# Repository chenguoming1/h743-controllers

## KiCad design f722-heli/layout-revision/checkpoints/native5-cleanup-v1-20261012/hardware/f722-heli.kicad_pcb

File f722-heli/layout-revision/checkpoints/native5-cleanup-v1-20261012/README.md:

# Native5 cleanup geometric checkpoint: WIP

This checkpoint preserves the adopted native5 routing geometry and its exact paired KiCad hardware. It is an unfinished engineering checkpoint. Five connections remain open, one of the 22 full actual-I/O protection cases remains incomplete, and the revised power/ground geometry has no current DC or transient/ESD qualification.

## Exact candidate

- Board SHA-256: `01b115302e079c6c7a2b1370ef4a089c19c7c2b54fd13e73cf2341db2dffc133`
- Native export SHA-256 after lossless decompression: `46d0b78c82003a3042e68ea2258fa40e5032499b3c3dc864594519c9178821ea`
- Original local recipe SHA-256: `0dfd4ea5db3699d0e1bc94254ddeb24d4ad1f0a3063fea49476f0aa3e17c50f3`
- Original physical audit SHA-256: `26ca9d2fc020c0b6bb8d0346441cec2a21c99e560304572752e54d91bfa256e7`
- Original reviewed partial-progress disposition SHA-256: `be2dfb278ef81590a2cb8b2abd86f47a1b82875ab9a294c7467eafcec9470bae`

`hardware/` contains the exact 61 paired source files, including the candidate PCB. All 60 other hardware files and all 558 pad identities and net assignments are unchanged. The adoption receipt is `evidence/geometric-checkpoint-review.json`. Earlier diagnostic receipts retain their original non-adoption status; they describe the state at the time each check ran.

## Routing change and measured result

U15 moves to the back of the board at `(27.721926, 21.185113)`, native orientation 0 degrees, using the physical top/bottom reflection. The earlier planning label “B180” is preserved as historical provenance; the explicit pad coordinates and native B0 pose are authoritative. Original RX/TX channel identities are retained. R34.1 reaches the actual RX I/O pad, TX uses its explicitly constructed NC bridge on the connector branch, CORE is reshaped, and U15 GND shares the existing C75 bulk-return barrel.

The cleanup removes the unused 18.027 mm TX arm, two barrels, and two overhanging stubs. It adds two exact 0.127 mm trim tracks while retaining all 94 previous recipe additions. Relative to the source7 board, the cumulative recipe has 64 removals, 87 added tracks, and nine added vias. The B-side trim uses the existing native junction, 0.5 nm from the rational midpoint; its actual fixed geometry has separate clearance and contact evidence.

Fresh native stages passed: refill/construction, netlist, ERC, DRC with schematic parity and all-track errors, and full paired verification. DRC reports five unconnected items, zero geometric error entries, zero schematic-parity entries, and three historical dangling MCU-via warnings. ERC reports zero violations. The five unfinished connections are PORT_C_RX_EXT from J11.1 to the clamp, PORT_C_TX_MCU, PORT_C_RX_MCU, FLASH_MOSI, and FLASH_SCK.

The independent physical audit found zero lost pad pairs against source7, native6, and the pre-cleanup native5 candidate. All 47 CORE pads, 133 GND pads, the four TX pads, changed real-pad contacts, new track endpoints and new via annuli pass the applicable connectivity/support checks. All previous successful actual-I/O cut cases are preserved: 21 of 22 full cases pass.

Full RX remains `INCOMPLETE_BEFORE_CUT`: J11.1 is isolated on F.Cu while R34.1, U15.1 and U15.10 are joined on B.Cu. The raw audit's aggregate is **false**, and its partial-RX gate remains **false**. A separate reviewed disposition passes only the allowed partial-progress criteria. It proves the completely inventoried cut partitions have no common conductive layer, explaining the empty same-layer gap list; it does not turn the full RX case into a pass. The full raw numerical/contact fields are retained in the path-normalized physical-audit derivative.

## Original mask failure and narrow representation fix

The first native assessment failed the strict reflected-mask polygon comparison. `representation/original-native-failure.json`, `comparison.json`, the saved moved-pad export, and the custom-copper diagnostic retain that failure and its evidence. The actual board geometry was not changed to repair the comparison.

The unchanged `representation_equivalence.py` and policy allow only the ten exact reflected U15 mask contours and the two custom GND outer contours to differ by a continuous symmetric boundary distance of at most 23 nm. This bound derives from two 10 nm KiCad polygon approximations plus integer-grid rounding. Exact inverse analytic primitives, all 558 pad settings, inside contours, UUIDs, nets, layers, sizes, centers, angles, vertex counts, single-component topology and zero-hole topology are still required. It is a representation comparison bound, never a physical clearance allowance. KiCad implementation citations are in the policy.

## Reproduction and verification

Run these commands from this checkpoint directory in the repository checkout:

```sh
python3 -B runtime/verify_saved.py
python3 -B runtime/check_controls.py
```

The saved replay verifies lossless compressed originals, the exact source-to-candidate recipe, 2,306 retained native records, all 558 pad identities/nets, all 96 additions, full schematic parity, native report counts, and the narrow 12-contour representation proof. Controls retain the original mask failure and reject over-bound/topology changes, altered added UUID/net/width, invalid partial-RX claims, and unsupported trim endpoints/fragments. These commands perform no native refill, routing search, or new physical audit. They need Python 3; the saved replay caps address space at 1.5 GiB and CPU time at 60 seconds.

`INPUT-REFERENCES.json` pins the unchanged source-board Git blob in the earlier joint-native7 checkpoint. It also pins the prior native6 gzip export as a historical comparison input. Those bytes are reused from the repository. Pass `--repository-root /path/to/checkout` if running the verification from a detached copy. Unique source and candidate native exports and candidate inside-contour evidence use deterministic gzip. `COMPRESSION-MANIFEST.json` records decompressed byte counts and SHA-256 values; exact originals reconstruct without loss.

For an optional fresh native rebuild in a new directory, use the official KiCad `10.0.6+dfsg-1` Python environment:

```sh
python3 -B runtime/replay_native.py --output /tmp/f722-native5-replay
```

The construction wrapper contains the exact ordered native mutation loop from the checked adapter, with portable arguments replacing execution-specific plumbing. It checks geometry, UUIDs and net identities against the saved candidate after refill. Packaging verified the saved geometry and function provenance; this portable native wrapper was syntax-checked but **not re-executed**. Byte-identical regeneration is not promised. Run fresh KiCad netlist, ERC, full DRC and schematic-parity checks before using any regenerated board. The raw hardware and compressed saved exports are the byte-exact checkpoint artifacts.

`SOURCE-PROVENANCE.json` distinguishes original source hashes, exact-byte files, path-normalized publication derivatives, and exact technical function extracts. A normalized recipe/report is not the original raw artifact: its publication SHA differs. Normalization changes path strings and omits execution-only metadata; numerical geometry and engineering results remain unchanged. `CONTENT-MANIFEST.json` binds the published file set; the external publication manifest also binds the immutable payload and complete additive Git tree.

## Qualification still open

The earlier native6 conditional DC result is historical: changed CORE/GND routing, drilling and fill make it stale for this candidate. C75 is the 47 µF +5V_PERIPH bulk capacitor, and its shared GND land/barrel can couple a TVS pulse into the peripheral supply return. Connectivity and DC conductance do not establish transient/ESD equivalence. No qualified dedicated-return replacement is demonstrated by the saved alternatives.

Current/thermal qualification, complete timing and reference-return review, the unresolved stock-I2C guarantee gap, manufacturing/assembly review, and flight qualification remain open. This checkpoint provides no manufacturing or flight-ready claim.

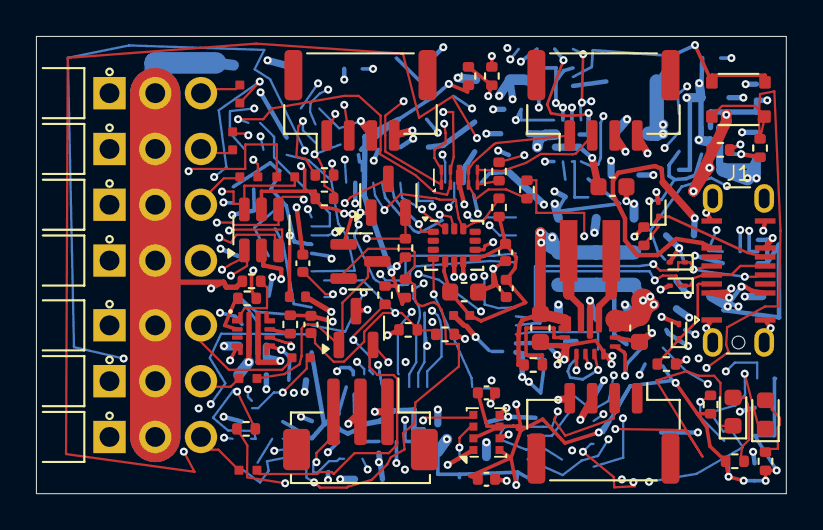
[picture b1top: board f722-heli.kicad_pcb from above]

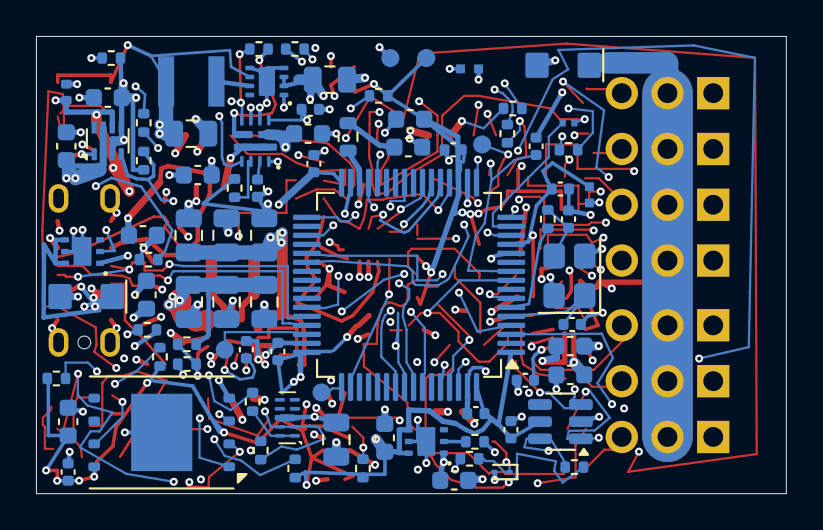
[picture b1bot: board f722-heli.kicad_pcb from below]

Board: 6 copper layers, 41.7 x 25.4 mm, 156 parts (84 on the bottom side), 95 nets.

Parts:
C1, C2, C3, C4, C6, C9, C10, C12, C14, C16, C17, C58: 100nF / 16V / X7R; C_0402_1005Metric
C5: 4.7uF / 10V / X5R; C_0603_1608Metric
C7, C61, C68, C70: 4.7uF / 10V / X7R; C_0603_1608Metric
C8, C60: 2.2uF / 10V / X7R(Murata); Murata_GRM155Z71A225KE44_0402
C11: 10nF / 16V / X7R; C_0402_1005Metric
C13: 2.2uF / 10V / X7R; C_0603_1608Metric
C15, C59, C65, C69: 1uF / 10V / X7R; C_0603_1608Metric
C18, C19: 15pF / 50V / C0G; C_0402_1005Metric
C20: 1uF / 16V / X7R; C_0603_1608Metric
C30, C31: 220nF / 16V / X7R; C_0402_1005Metric
C50: 3.3nF / 50V / C0G; C_0402_1005Metric
C51, C52, C64, C74: 1uF / 25V / X7R; C_0603_1608Metric
C53, C54, C66, C71: 22uF / 25V / X5R; C_0805_2012Metric
C55, C56, C57, C75: 47uF / 10V / X5R; C_0805_2012Metric
C62: 100nF / 25V / X7R; C_0402_1005Metric
C63: 1nF / 50V / C0G; C_0402_1005Metric
C67: 22uF / 10V / X7R; C_0805_2012Metric
C72, C73: 10uF / 25V / X5R / HF; C_0603_1608Metric
D1: GREEN; LED_0603_1608Metric
D2: RED; LED_0603_1608Metric
D3, D4, D5, D6, D7: ESD9M5.0ST5G; D_SOD-923
D8: SMF5.0A / transient only; Littelfuse_SMF_SOD123FL
D9: SMF15CA / bidirectional; Littelfuse_SMF_SOD123FL
FB1, FB2: 600R@100MHz / 0.3A; Murata_BLM15AG_0402
J1: USB4145-03-0170-C; USB_C_Receptacle_GCT_USB4145-03-0170-C_16P_Vertical
J2: S1 / GND-VX-S; Samtec_HTSW-101-08-L-T-RA_TripleRow_OpenEdgeSilk
J3: S2 / GND-VX-S; Samtec_HTSW-101-08-L-T-RA_TripleRow_OpenEdgeSilk
J4: S3 / GND-VX-S; Samtec_HTSW-101-08-L-T-RA_TripleRow_OpenEdgeSilk
J5: TAIL / GND-VX-S; Samtec_HTSW-101-08-L-T-RA_TripleRow_OpenEdgeSilk
J6: ESC / GND-VX-S; Samtec_HTSW-101-08-L-T-RA_TripleRow_OpenEdgeSilk
J7: RPM / GND-VX-S; Samtec_HTSW-101-08-L-T-RA_TripleRow_OpenEdgeSilk
J8: SBUS / GND-VX-S; Samtec_HTSW-101-08-L-T-RA_TripleRow_OpenEdgeSilk
J9: PORT A / JST GH; JST_GH_BM04B-GHS-TBT_1x04-1MP_P1.25mm_Vertical
J10: PORT B / JST GH; JST_GH_BM04B-GHS-TBT_1x04-1MP_P1.25mm_Vertical
J11: PORT C / JST GH; JST_GH_BM04B-GHS-TBT_1x04-1MP_P1.25mm_Vertical
J12: DSM / JST ZH; JST_ZH_B3B-ZR-SM4-TF_1x03-1MP_P1.50mm_Vertical
L1: 1.5uH / XGL4020-152MEC; Coilcraft_XGL4020
L2: 3.3uH / DFE322512F; Murata_DFE322512F
Q1, Q2: BSS138LT1G; SOT-23
R1, R3, R4, R6, R64, R69: 10k / 1%; R_0402_1005Metric
R2, R7, R8, R10, R11: 2.2k / 1%; R_0402_1005Metric
R5: 10k / 1%; R_0402_1005Metric_R5_ClearPin1Silk
R9: 0R / drive tuning; R_0402_1005Metric
R14, R15: 5.1k / 1%; R_0402_1005Metric
R16: 0.12R / 1% / VCAP ESR; R_Panasonic_ERJ3R_0603
R20, R21, R22, R23, R24, R25, R26: 470R / 1% / 0.20W; Panasonic_ERJPA2_0402
R30, R32, R33, R34, R35, R38: 22R / 1%; R_0402_1005Metric
R31: 22R / 1%; R_0201_0603Metric_YAGEO_AC
R36, R37: 4.7k / 1%; R_0402_1005Metric
R39, R45: 220R / 1%; R_0402_1005Metric
R40: 105k / 0.1%; R_0402_1005Metric
R41: 20.0k / 0.1%; R_0402_1005Metric
R42: 68.0k / 0.1%; R_0402_1005Metric
R43, R44: 16.0k / 0.1%; R_0402_1005Metric
R50: 1.5M / 1%; R_0402_1005Metric
R51: 390k / 1%; R_0402_1005Metric
R52: 750R / 1%; R_0402_1005Metric
R53: 4.7k / 1%; Panasonic_ERJPA2_0402
R54: 53.6k / 0.1%; R_0402_1005Metric
R55, R61, R63: 10.0k / 0.1%; R_0402_1005Metric
R56, R57: 100k / 1%; R_0402_1005Metric
R58: 47k / 1%; R_0402_1005Metric
R60: 18.0k / 0.1%; R_0402_1005Metric
R62: 12.7k / 0.1%; R_0402_1005Metric
R65: 330k / 1%; R_0402_1005Metric
R66: 80.6k / 1%; R_0402_1005Metric
R67: 66.5k / 1%; R_0402_1005Metric
R68: 1k / 1%; R_0402_1005Metric
R70: 45.3k / 1%; R_0402_1005Metric
R71: 100k / 1% / ROM RX idle; R_0402_1005Metric
SW1: BOOT / KMT031NGJLHS; CK_KMT031NGJLHS
TP1: SWD SWDIO; TestPoint_Pad_D1.0mm_Compact
TP2: SWD SWCLK; TestPoint_Pad_D1.0mm_Compact
TP3: SWD +3V3_CORE; TestPoint_Pad_D1.0mm_Compact
TP4: SWD GND; TestPoint_Pad_D1.0mm_Compact
TP5: SWD NRST; TestPoint_Pad_D1.0mm_Compact
U1: STM32F722RET6; LQFP-64_10x10mm_P0.5mm
U2: ICM-42688-P; LGA-14_3x2.5mm_P0.5mm_LayoutBorder3x4y
U3: W25N01GVZEIG / 128MiB; WSON-8-1EP_8x6mm_P1.27mm_EP3.4x4.3mm
U4: DPS368XTSA1 / 0x76; Infineon_DPS368_VLGA-8_2.5x2mm_SMD
U5: TPS259472ARPWR; Texas_RPW0010A_TPS259472_2x2mm
U6: TPS63070RNMR / nominal 5.088V; Texas_RNM0015A_TPS63070_2.5x3mm
U7: TPS2117DRLR / ABC priority mux; SOT-583-8
U8: TPS2121RUXR / BEC-priority core mux; Texas_RUX0012A_TPS2121_2x2.5mm
U9: TPS62162DSGR / 3.3V 1A; Texas_DSG0008A_TPS62162_2x2mm_EP0.9x1.6mm
U10: TPS2553DRVR / USB input limit; Texas_DRV0006A_TPS2553_2x2mm_EP1x1.6mm
U11: TPS2553DRVR / DSM output limit; Texas_DRV0006A_TPS2553_2x2mm_EP1x1.6mm
U12, U13: USBLC6-4SC6 / header clamp; SOT-23-6
U14, U15: TPD4E05U06DQAR / UART ESD; Texas_DQA0010B_TPD4E05U06_2.5x1mm
U16: PESD15VS2UT,215 / 15V ESD; SOT-23
Y1: 8MHz / CL10pF / TAXM8M4RDBCCT2T; Crystal_SMD_3225-4Pin_3.2x2.5mm

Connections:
+3V3_ANALOG: C8.1, C9.1, FB1.2, U1.13
+3V3_CORE: C1.1, C2.1, C3.1, C4.1, C5.1, C6.1, C14.1, C15.1, C16.1, C17.1, C67.1, C69.1, FB1.1, FB2.1, L2.2, Q1.1, Q2.1, R1.1, R4.1, R5.1, R6.1, R7.1, R8.1, R10.1, R11.1, R36.1, R37.1, R62.1, R64.1, R71.1, SW1.1, TP3.1, U1.1, U1.19, U1.32, U1.48, U1.64, U3.8, U4.2, U4.6, U4.8, U9.6, U11.4, U11.6, U12.5, U13.5
+3V3_DSM: C70.1, J12.1, U11.1
+3V3_IMU: C11.1, C12.1, C13.1, FB2.2, R3.1, U2.5, U2.8
+5V_BEC: C55.1, C56.1, C57.1, C59.1, C73.1, R54.1, R56.1, R58.1, U6.7, U6.8, U7.3, U7.5
+5V_PERIPH: C61.1, C75.1, J9.3, J10.3, J11.3, R42.1, U7.2, U7.7
ABC_EN: R57.2, U6.14
ABC_FB: R54.2, R55.1, U6.5
ABC_L1: L1.1, U6.11
ABC_L2: L1.2, U6.9
ABC_PG: R56.2, U6.2, U7.4
ABC_VAUX: C58.1, U6.3
ADC_BEC: C30.1, R40.2, R41.1, U1.9
ADC_BUS: C31.1, R42.2, R43.1, U1.10
ADC_DIV_MID: R43.2, R44.1
BARO_SCL: R7.2, U1.61, U4.4
BARO_SDA: R8.2, U1.62, U4.3
BOOT0: R2.1, SW1.2, U1.60
CORE_BUCK_IN: C66.1, C74.1, U8.1, U8.8, U9.2, U9.3
CORE_ILIM: R66.1, U8.10
CORE_MUX_ST: R64.2, R65.1, U8.9
CORE_PRIORITY: R60.2, R61.1, R65.2, U8.6
CORE_REF: C63.1, R62.2, R63.1, U8.3
CORE_SS: C62.1, U8.11
CORE_SW: L2.1, U9.7
D1_A: D1.2, R10.2
D2_A: D2.2, R11.2
DSM_ILIM: R70.1, U11.2
DSM_RX_EXT: D7.1, J12.3, R38.1
DSM_RX_MCU: R38.2, R71.2, U1.43
EFUSE_DVDT: C50.1, U5.7
EFUSE_EN: R50.2, U5.1
EFUSE_ILM: R52.1, U5.9
EFUSE_OVC: R51.1, U5.2
ESC_EXT: J6.3, R24.1
ESC_MCU: R24.2, U1.58, U13.3
FLASH_CS: R4.2, U1.33, U3.1
FLASH_HOLD_N: R6.2, U3.7
FLASH_MISO: U1.35, U3.2
FLASH_MOSI: U1.36, U3.5
FLASH_SCK: U1.34, U3.6
FLASH_WP_N: R5.2, U3.3
GND: C1.2, C2.2, C3.2, C4.2, C5.2, C6.2, C7.2, C8.2, C9.2, C10.2, C11.2, C12.2, C13.2, C14.2, C15.2, C16.2, C17.2, C18.2, C19.2, C20.2, C30.2, C31.2, C50.2, C51.2, C52.2, C53.2, C54.2, C55.2, C56.2, C57.2, C58.2, C59.2, C60.2, C61.2, C62.2, C63.2, C64.2, C65.2, C66.2, C67.2, C68.2, C69.2, C70.2, C71.2, C72.2, C73.2, C74.2, C75.2, D3.2, D4.2, D5.2, D6.2, D7.2, D8.2, D9.2, J1.A1, J1.A12, J1.B1, J1.B12, J1.S1, J2.1, J3.1, J4.1, J5.1, J6.1, J7.1, J8.1, J9.4, J10.4, J11.4, J12.2, R2.2, R14.2, R15.2, R41.2, R44.2, R51.2, R52.2, R53.2, R55.2, R58.2, R61.2, R63.2, R66.2, R67.2, R68.2, R69.2, R70.2, TP4.1, U1.12, U1.18, U1.31, U1.47, U1.63, U2.6, U2.7, U2.9, U3.4, U3.9, U4.1, U4.5, U4.7, U5.4, U5.8, U6.1, U6.4, U6.6, U6.10, U6.15, U7.1, U8.4, U8.5, U8.12, U9.1, U9.4, U9.5, U9.9, U10.5, U10.7, U11.5, U11.7, U12.2, U13.2, U14.3, U14.8, U15.3, U15.8, U16.3, Y1.2, Y1.4
HSE_IN: C18.1, U1.5, Y1.1
HSE_OUT: R9.1, U1.6
HSE_XTAL_OUT: C19.1, R9.2, Y1.3
IMU_CS: R3.2, U1.20, U2.12
IMU_INT: U1.50, U2.4
IMU_MISO: U1.22, U2.1
IMU_MOSI: U1.23, U2.14
IMU_SCK: U1.21, U2.13
LED_GREEN_K: D1.1, U1.3
LED_RED_K: D2.1, U1.4
NRST: C10.1, R1.2, TP5.1, U1.7
PORT_A_RX_EXT: J9.1, R30.1, U14.1, U14.10
PORT_A_RX_MCU: R30.2, U1.14
PORT_A_TX_EXT: J9.2, R31.1, U14.2, U14.9
PORT_A_TX_MCU: R31.2, U1.15
PORT_B_RX_EXT: J10.1, R32.1, U14.4, U14.7
PORT_B_RX_MCU: R32.2, U1.37
PORT_B_TX_EXT: J10.2, R33.1, U14.5, U14.6
PORT_B_TX_MCU: R33.2, U1.38
PORT_C_RX_EXT: J11.1, R34.1, U15.1, U15.10
PORT_C_RX_MCU: R34.2, U1.28
PORT_C_TX_EXT: J11.2, R35.1, U15.2, U15.9
PORT_C_TX_MCU: R35.2, U1.29
RPM_EXT: J7.3, R25.1
RPM_HV: Q1.3, R25.2, U16.1
RPM_LV: Q1.2, R36.2, R39.1
RPM_MCU: R39.2, U1.16, U13.6
SBUS_EXT: J8.3, R26.1
SBUS_HV: Q2.3, R26.2, U16.2
SBUS_LV: Q2.2, R37.2, R45.1
SBUS_MCU: R45.2, U1.17, U13.1
SERVO1_EXT: J2.3, R20.1
SERVO1_MCU: R20.2, U1.56, U12.1
SERVO2_EXT: J3.3, R21.1
SERVO2_MCU: R21.2, U1.57, U12.3
SERVO3_EXT: J4.3, R22.1
SERVO3_MCU: R22.2, U1.25, U12.4
SWCLK: TP2.1, U1.49
SWDIO: TP1.1, U1.46
TAIL_EXT: J5.3, R23.1
TAIL_MCU: R23.2, U1.55, U12.6
USB_CC1: D5.1, J1.A5, R14.1
USB_CC2: D6.1, J1.B5, R15.1
USB_ILIM: R67.1, U10.2
USB_LIMITED: C60.1, C65.1, C68.1, R68.1, U7.6, U8.2, U10.1
USB_N: D4.1, J1.A7, J1.B7, U1.44
USB_P: D3.1, J1.A6, J1.B6, U1.45
USB_VBUS_RAW: C20.1, D8.1, J1.A4, J1.A9, J1.B4, J1.B9, R69.1, U10.4, U10.6
VCAP: R16.1, U1.30
VCAP_CAP: C7.1, R16.2
VX_PROTECTED: C52.1, C53.1, C54.1, C64.1, C71.1, C72.1, R53.1, R57.1, R60.1, U5.6, U6.12, U6.13, U8.7
VX_RAW: C51.1, D9.1, J2.2, J3.2, J4.2, J5.2, J6.2, J7.2, J8.2, R40.1, R50.1, U5.5

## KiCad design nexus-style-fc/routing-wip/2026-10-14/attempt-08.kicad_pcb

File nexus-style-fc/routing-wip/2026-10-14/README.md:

# Connected local-clearance experiment: unfinished

`attempt-08.kicad_pcb` is a review-only experimental board, separate from canonical hardware. Native KiCad 10 reports **361 clearance errors, 0 opens and 0 schematic-parity issues**. It is not compliant and must not feed manufacturing exports.

The original connected board was used, all 937 subminimum segments were widened to at least 0.127 mm, and 66 bounded local patches adjusted route coordinates by at most 0.07977 mm. Each patch protected pad landings, existing copper contacts including off-center via contacts, original locks and wide power segments. Native refill/DRC is authoritative: the widened seed had 458 clearance errors; this candidate has 361, with no new dangling-copper warnings and the same 54 historical silkscreen warnings. All 361 remaining errors are visible in `attempt-08-drc.json`.

Source invariants pass for all 88 footprint definitions, pad/net assignments, placements, outline, physical stack, setup and zone/keepout definitions. All 1,450 segments meet the 0.127 mm minimum, and all 225 vias retain 0.45/0.20 mm geometry. Aggregate original power-net width floors pass. Those checks do not qualify branch ampacity, USB impedance, finite return paths, thermal behavior or flight operation.

The original 18 vias drilling pasted SMT lands remain at their original locations, producing 19 contact pairs. No new drill/paste contact was introduced. Ordinary tenting is not evidence of a filled/capped assembly process; removal or an approved manufacturing disposition remains necessary.

## Evidence and reproduction

- `attempt-08-manifest.json` binds candidate/report hashes, canonical companion hashes, native invocation and failure counts.
- `attempt-08-drc.json` is native KiCad 10.0.7 DRC after refill/save, all track errors, full severity and schematic parity.
- `attempt-08-validation.json` checks the exact source-bound invariants and geometry. Overall status is **fail** due to clearance errors.

To recheck, use an isolated copy of the complete Nexus project and its libraries. In that copy only, replace `hardware/nexus-style-fc.kicad_pcb` with this candidate. Keep the main project/rule/schematic files matching the manifest hashes, then run the recorded KiCad 10 command. Do not replace the canonical PCB or export CAM from this experiment.

A separate six-layer global reroute reached zero geometry errors but still had 62 opens and 51 dangling items after safe source-power restoration. That disconnected candidate is not the connected local-repair candidate published here. Neither result is full compliance.

Canonical main/header PCBs remain unchanged from source. The 11 fixed header-contact edge violations, tab/slot interference, USB/reference-path review, power qualification and manufacturing release remain open. Historical CAM/BOM outputs are on hold.

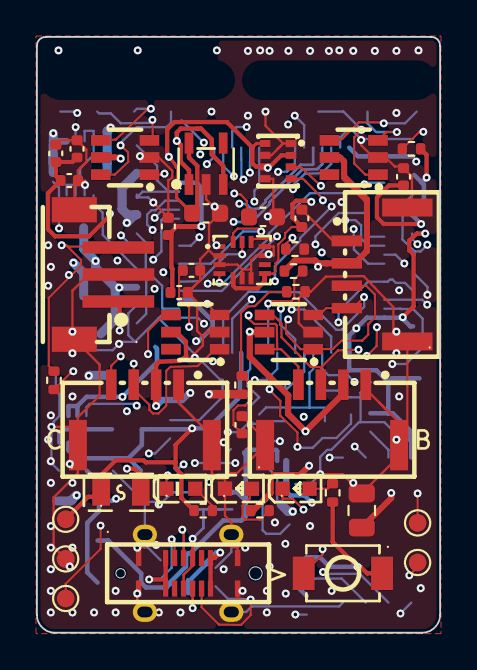
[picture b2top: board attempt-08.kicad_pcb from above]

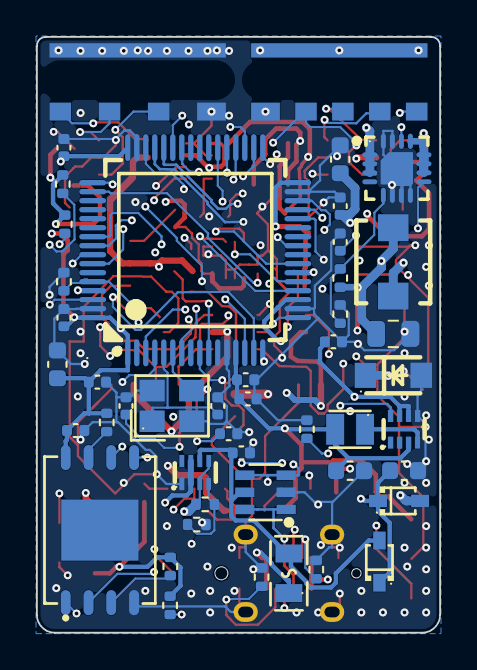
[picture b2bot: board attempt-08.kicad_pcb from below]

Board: 6 copper layers, 22.4 x 33.1 mm, 88 parts (44 on the bottom side), 62 nets.

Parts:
C1, C2, C3, C4, C7, C8, C10, C13, C16, C17, C20, C22, C29, C30: 100nF; C_0402_1005Metric
C5, C9, C27: 4.7uF; C_0603_1608Metric
C6, C18, C25: 1uF; C_0402_1005Metric
C11, C12: 30pF; C_0402_1005Metric
C14: 2.2uF; C_0402_1005Metric
C15: 10nF; C_0402_1005Metric
C19: 2.2uF; C_0603_1608Metric
C21: 10uF; C_0603_1608Metric
C23: 3.3nF; C_0402_1005Metric
C24, C26: 22uF; C_0805_2012Metric
C28: 22uF; C_0603_1608Metric
D1: LED1 yellow-green; LED0603-RD_GREEN
D2: LED2 red; LED0603-RD_RED
D3: Power LED blue; LED0603-RD_BLUE
D4: SMF13A; SOD-123FL_L2.8-W1.8-LS3.6-RD
D5, D6: B5819WS; SOD-323_L1.8-W1.3-LS2.5-RD
F1, F2: 0.5A PTC; F0805
J1: Header child board; HeaderBoard_Joint
J2: DSM (UART1); CONN-SMD_B3B-ZR-SM4-TF
J3: A-CRSF (UART4); CONN-SMD_4P-P1.25_BM04B-GHS-TBT-LF-SN
J4: C (UART3); CONN-SMD_4P-P1.25_BM04B-GHS-TBT-LF-SN
J5: B (UART6); CONN-SMD_4P-P1.25_BM04B-GHS-TBT-LF-SN
J6: USB-C vertical; USB-C-SMD_TYPE-C-31-D-06
L1: 2.2uH 3A; IND-SMD_L4.6-W4.1
L2: 2.2uH; IND-SMD_L2.0-W1.6
R1, R5, R8, R9, R10, R17, R19: 10k; R_0402_1005Metric
R2, R3, R4, R22: 1k; R_0402_1005Metric
R6, R7: 2.2k; R_0402_1005Metric
R11: 120k; R_0402_1005Metric
R12: 22k; R_0402_1005Metric
R13: 100k; R_0402_1005Metric
R14: 27k; R_0402_1005Metric
R15: 27.4k; R_0402_1005Metric
R16: 52.3k; R_0402_1005Metric
R18: 21k; R_0402_1005Metric
R20, R21: 5.1k; R_0402_1005Metric
SW1: BOOT; SW-SMD_L3.9-W3.0-P4.45
TP1: SWDIO; TestPoint_Pad_D1.0mm
TP2: SWCLK; TestPoint_Pad_D1.0mm
TP3: 3V3; TestPoint_Pad_D1.0mm
TP4: GND; TestPoint_Pad_D1.0mm
TP5: NRST; TestPoint_Pad_D1.0mm
U1: STM32F722RET6; LQFP-64_L10.0-W10.0-P0.50-LS12.0-BL
U2: ICM-42688-P; LGA-14_L3.0-W2.5-P0.50-TL
U3: DPS368XTSA1; LGA-8_L2.5-W2.0-P0.65-TR_DPS368
U4: W25N01GVZEIG; WSON-8_L8.0-W6.10-P1.27-BL-EP
U5: TPS62130RGTR; QFN-16_L3.0-W3.0-P0.50-TL-EP1.7
U7: USBLC6-2SC6; SOT-23-6_L2.9-W1.6-P0.95-LS2.8-BL
U9: TPS2116DRLR; SOT-583-8_L2.1-W1.6-P0.50-LS1.6-BL
U10: TPS70933DBVR; SOT-23-5_L3.0-W1.7-P0.95-LS2.8-BL
U11, U12, U13, U15: SRV05-4; SOT-23-6_L2.9-W1.6-P0.95-LS2.8-BR
U14: TPS629210DRLR; SOT-5X3-8_L2.1-W1.2-P0.50-LS1.6-BL_DRL0008A
Y1: 8MHz 20pF; CRYSTAL-SMD_4P-L3.2-W2.5-BL

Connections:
3V3: C1.1, C2.1, C3.1, C4.1, C5.1, C6.1, C7.1, C8.1, C20.1, C28.1, F2.1, L2.2, R2.1, R3.1, R8.2, R9.2, R10.2, SW1.2, TP3.1, U1.1, U1.13, U1.19, U1.32, U1.48, U1.64, U4.8, U14.3
3V3_DSM: F2.2, J2.1
3V3_SENS: C13.1, C14.1, C15.1, C16.1, C17.1, C19.1, R5.2, R6.2, R7.2, U2.5, U2.8, U3.2, U3.6, U3.8, U10.5
5V: C26.1, J3.2, J4.2, J5.2, R4.1, R18.1, U9.2, U9.7, U11.5, U12.5, U13.5, U15.5
5V_BUCK: C24.1, L1.2, R11.1, R13.1, U5.14, U9.3, U9.5
5V_SENSE: C30.1, R18.2, R19.1, U1.10
A_RX: J3.3, U1.14, U13.1
A_TX: J3.4, U1.15, U13.3
BOOT0: R1.1, SW1.1, U1.60
B_RX: J5.3, U1.37, U13.4
B_TX: J5.4, U1.38, U13.6
CC1: J6.A5, R20.1
CC2: J6.B5, R21.1
C_RX: J4.3, U1.28, U15.1
C_TX: J4.4, U1.29, U15.3
DSM_DATA: J2.3, R22.2, U1.43, U15.4
DSM_TX: R22.1, U1.42
ESC: J1.5, U1.58, U11.4
FB_5V: R11.2, R12.1, U5.5
FLASH_CS: R8.1, U1.33, U4.1
FLASH_HOLD: R10.1, U4.7
FLASH_WP: R9.1, U4.3
GND: C1.2, C2.2, C3.2, C4.2, C5.2, C6.2, C7.2, C8.2, C9.2, C10.2, C11.2, C12.2, C13.2, C14.2, C15.2, C16.2, C17.2, C18.2, C19.2, C20.2, C21.2, C22.2, C23.2, C24.2, C25.2, C26.2, C27.2, C28.2, C29.2, C30.2, D3.1, D4.2, J1.2, J2.2, J2.4, J2.5, J3.1, J3.5, J3.6, J4.1, J4.5, J4.6, J5.1, J5.5, J5.6, J6.A1, J6.A12, J6.B1, J6.B12, J6.EP, R1.2, R12.2, R14.2, R15.2, R17.2, R19.2, R20.2, R21.2, TP4.1, U1.12, U1.18, U1.31, U1.47, U1.63, U2.2, U2.3, U2.6, U2.7, U2.10, U2.11, U3.1, U3.5, U3.7, U4.4, U5.6, U5.7, U5.8, U5.15, U5.16, U5.17, U7.2, U9.1, U10.2, U11.2, U12.2, U13.2, U14.5, U15.2, Y1.2, Y1.4
I2C1_SCL: R6.1, U1.61, U3.4
I2C1_SDA: R7.1, U1.62, U3.3
IMU_CS: R5.1, U1.20, U2.12
IMU_INT: U1.50, U2.4
LED1_A: D1.2, R2.2
LED1_K: D1.1, U1.3
LED2_A: D2.2, R3.2
LED2_K: D2.1, U1.4
LED3_A: D3.2, R4.2
NRST: C10.1, TP5.1, U1.7
OSC_IN: C11.1, U1.5, Y1.1
OSC_OUT: C12.1, U1.6, Y1.3
PR1: R13.2, R14.1, U9.4
RPM: J1.4, U1.16, U11.3
S1: J1.9, U1.56, U12.4
S2: J1.8, U1.57, U12.3
S3: J1.7, U1.25, U12.1
SBUS: J1.3, U1.17, U11.1
SCONF: R15.1, U14.8
SPI1_MISO: U1.22, U2.1
SPI1_MOSI: U1.23, U2.14
SPI1_SCK: U1.21, U2.13
SPI2_MISO: U1.35, U4.2
SPI2_MOSI: U1.36, U4.5
SPI2_SCK: U1.34, U4.6
SS_5V: C23.1, U5.9
SWCLK: TP2.1, U1.49
SWDIO: TP1.1, U1.46
SW_3V3: L2.1, U14.4
SW_5V: L1.1, U5.1, U5.2, U5.3
TAIL: J1.6, U1.55, U11.6
USB_DM: J6.A7, J6.B7, U1.44, U7.1, U7.6
USB_DP: J6.A6, J6.B6, U1.45, U7.3, U7.4
VBUS: C25.1, D6.2, F1.2, U7.5, U9.6
VBUS_C: F1.1, J6.A4, J6.A9, J6.B4, J6.B9
VCAP: C9.1, U1.30
VSYS: C18.1, C27.1, D5.1, D6.1, U10.1, U10.3, U14.6, U14.7
VX: C21.1, C22.1, D4.1, D5.2, J1.1, R16.1, U5.10, U5.11, U5.12, U5.13
VX_SENSE: C29.1, R16.2, R17.1, U1.9

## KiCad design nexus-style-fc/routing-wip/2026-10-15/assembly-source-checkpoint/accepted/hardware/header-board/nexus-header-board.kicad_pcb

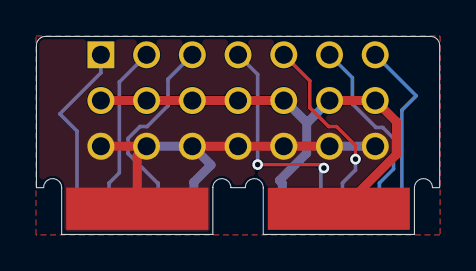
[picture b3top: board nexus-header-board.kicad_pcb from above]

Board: 2 copper layers, 22.4 x 11.0 mm, 12 parts (0 on the bottom side), 9 nets.

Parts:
J1: Servo header 3x7; Header_3x07_P2.54_Vertical_Servo
K1: GND strip; ChildBoard_TabStrip_W7.892
K2: VX strip; ChildBoard_TabStrip_W7.892
P1: S1 tab pad; ChildBoard_TabPad_Sig
P2: S2 tab pad; ChildBoard_TabPad_Sig
P3: S3 tab pad; ChildBoard_TabPad_Sig
P4: TAIL tab pad; ChildBoard_TabPad_Sig
P5: ESC tab pad; ChildBoard_TabPad_Sig
P6: RPM tab pad; ChildBoard_TabPad_Sig
P7: SBUS tab pad; ChildBoard_TabPad_Sig
T1: GND tab pad; ChildBoard_TabPad_Pwr
T2: VX tab pad; ChildBoard_TabPad_Pwr

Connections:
ESC: J1.13, P5.1
GND: J1.3, J1.6, J1.9, J1.12, J1.15, J1.18, J1.21, K1.1, T1.1
RPM: J1.16, P6.1
S1: J1.1, P1.1
S2: J1.4, P2.1
S3: J1.7, P3.1
SBUS: J1.19, P7.1
TAIL: J1.10, P4.1
VX: J1.2, J1.5, J1.8, J1.11, J1.14, J1.17, J1.20, K2.1, T2.1
